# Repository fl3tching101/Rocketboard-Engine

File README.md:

# Rocketboard-Engine
Board which carries the full brains/powerhouse of a keyboard.

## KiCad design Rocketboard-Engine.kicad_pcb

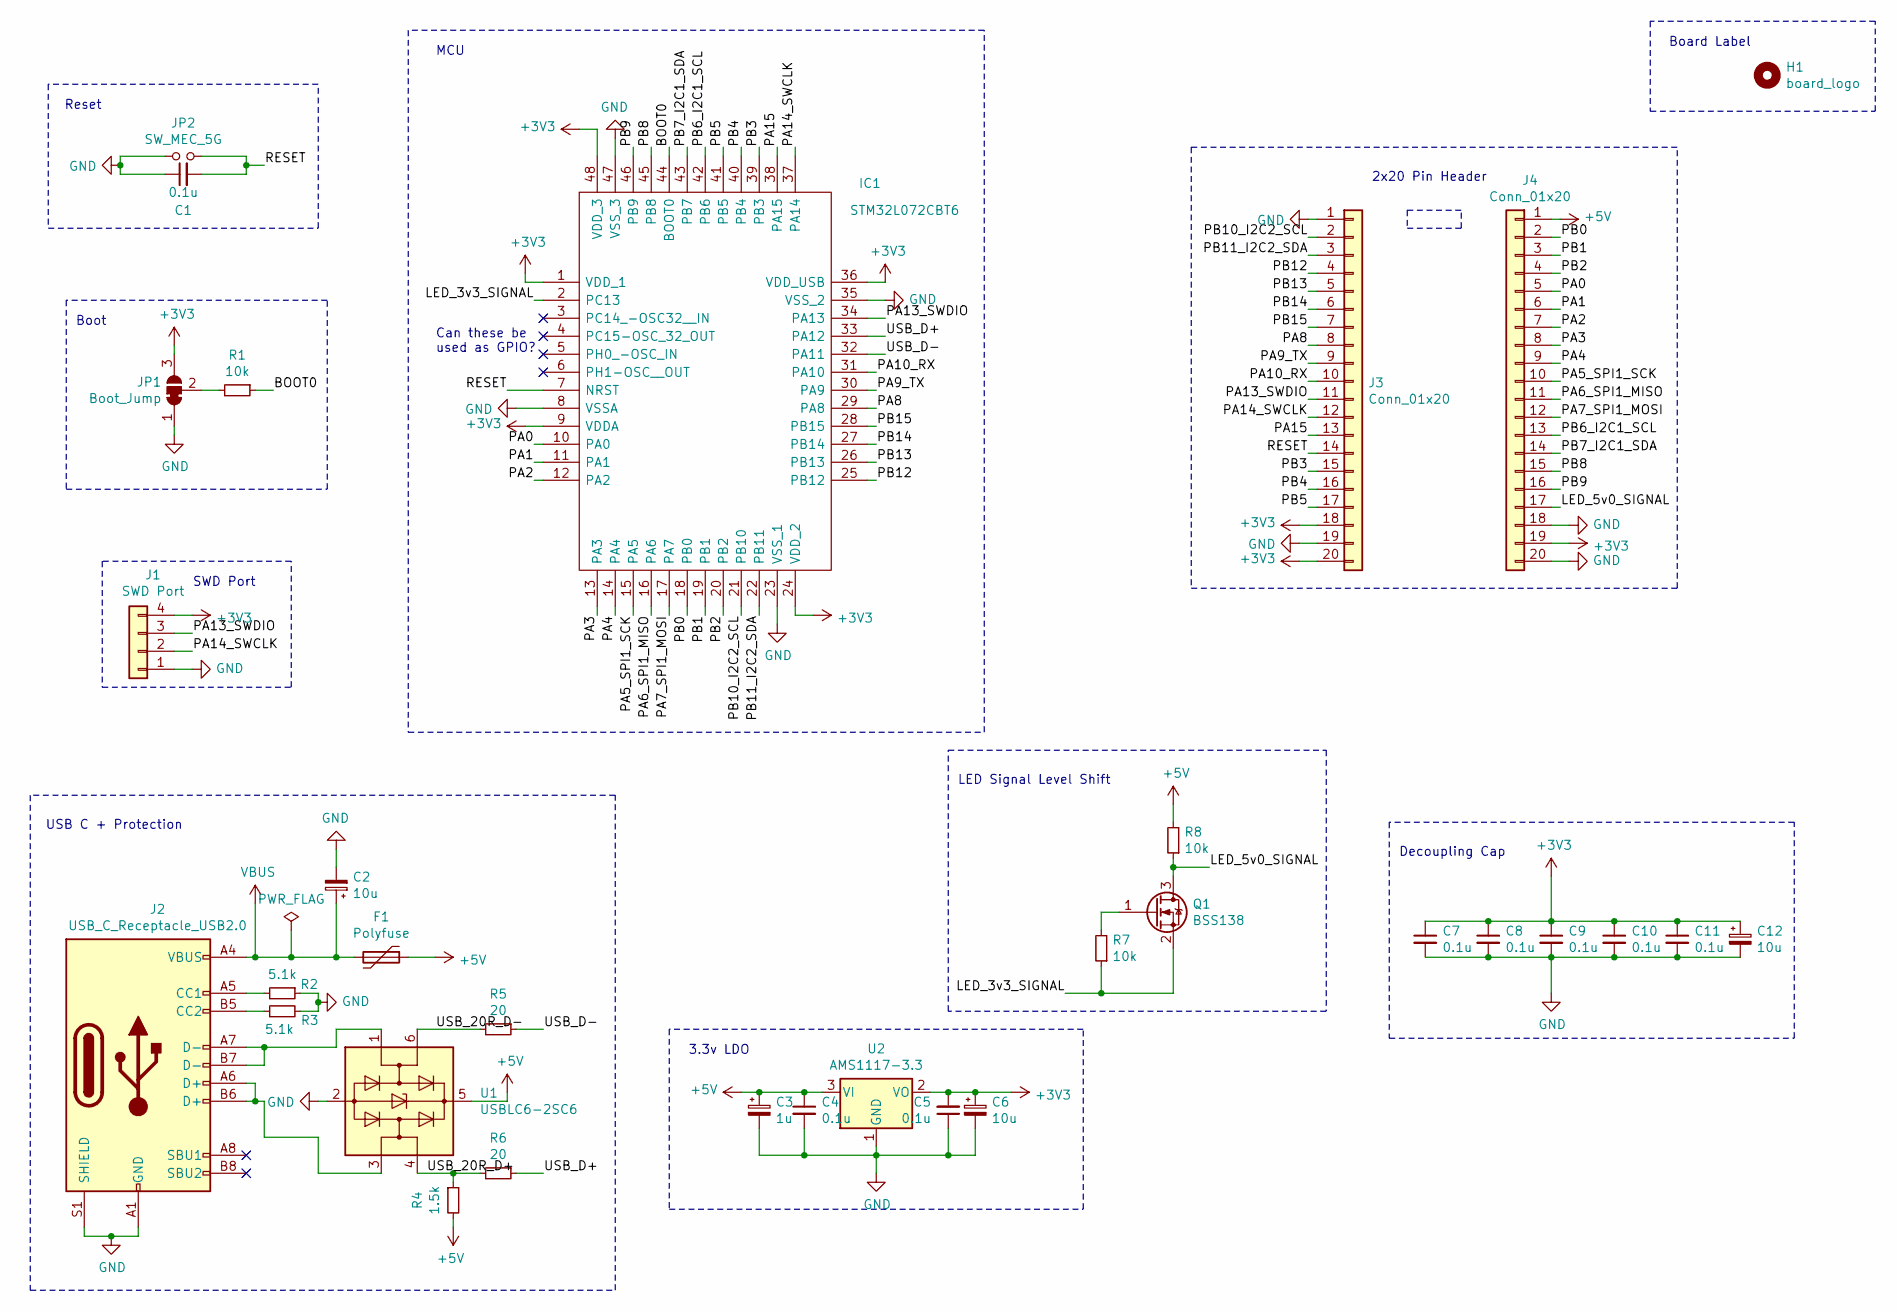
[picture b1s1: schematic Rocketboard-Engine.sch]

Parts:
C1, C4, C5, C7, C8, C9, C10, C11: 0.1u; C_0402_1005Metric
C2, C6, C12: 10u; CP_EIA-3216-10_Kemet-I
C3: 1u; C_0603_1608Metric
F1: Polyfuse; R_0805_2012Metric
H1: board_logo; board-title
IC1: STM32L072CBT6; LQFP-48_7x7mm_P0.5mm; Manufacturer_Part_Number STM32L072CBT6; Mouser Part Number 511-STM32L072CBT6
J1: SWD Port; PinHeader_1x04_P2.54mm_Vertical
J2: USB_C_Receptacle_USB2.0; USB_C_Receptacle_Palconn_UTC16-G
J3, J4: Conn_01x20; PinHeader_1x20_P2.54mm_Vertical
JP1: Boot_Jump; SolderJumper-3_P1.3mm_Bridged12_Pad1.0x1.5mm
JP2: SW_MEC_5G; SolderJumper-2_P1.3mm_Open_Pad1.0x1.5mm
Q1: BSS138; SOT-23
R1, R7, R8: 10k; R_0603_1608Metric
R2, R3: 5.1k; R_0603_1608Metric
R4: 1.5k; R_0603_1608Metric
R5, R6: 20; R_0603_1608Metric
U1: USBLC6-2SC6; SOT-23-6
U2: AMS1117-3.3; SOT-223-3_TabPin2

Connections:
+3V3: C5.2, C6.1, C7.1, C8.1, C9.1, C10.1, C11.1, C12.1, IC1.1 (VDD_1), IC1.9 (VDDA), IC1.24 (VDD_2), IC1.36 (VDD_USB), IC1.48 (VDD_3), J1.4, J3.18, J3.20, J4.19, JP1.3 (B), U2.2 (VO)
+5V: C3.1, C4.1, F1.1, J4.1, R4.2, R8.2, U1.5 (VBUS), U2.3 (VI)
/BOOT0: IC1.44 (BOOT0), R1.1
/LED_3v3_SIGNAL: IC1.2 (PC13), Q1.2 (S), R7.1
/LED_5v0_SIGNAL: J4.17, Q1.3 (D), R8.1
/PA0: IC1.10 (PA0), J4.5
/PA1: IC1.11 (PA1), J4.6
/PA2: IC1.12 (PA2), J4.7
/PA3: IC1.13 (PA3), J4.8
/PA4: IC1.14 (PA4), J4.9
/PA5_SPI1_SCK: IC1.15 (PA5), J4.10
/PA6_SPI1_MISO: IC1.16 (PA6), J4.11
/PA7_SPI1_MOSI: IC1.17 (PA7), J4.12
/PA8: IC1.29 (PA8), J3.8
/PA9_TX: IC1.30 (PA9), J3.9
/PA10_RX: IC1.31 (PA10), J3.10
/PA13_SWDIO: IC1.34 (PA13), J1.3, J3.11
/PA14_SWCLK: IC1.37 (PA14), J1.2, J3.12
/PA15: IC1.38 (PA15), J3.13
/PB0: IC1.18 (PB0), J4.2
/PB1: IC1.19 (PB1), J4.3
/PB2: IC1.20 (PB2), J4.4
/PB3: IC1.39 (PB3), J3.15
/PB4: IC1.40 (PB4), J3.16
/PB5: IC1.41 (PB5), J3.17
/PB6_I2C1_SCL: IC1.42 (PB6), J4.13
/PB7_I2C1_SDA: IC1.43 (PB7), J4.14
/PB8: IC1.45 (PB8), J4.15
/PB9: IC1.46 (PB9), J4.16
/PB10_I2C2_SCL: IC1.21 (PB10), J3.2
/PB11_I2C2_SDA: IC1.22 (PB11), J3.3
/PB12: IC1.25 (PB12), J3.4
/PB13: IC1.26 (PB13), J3.5
/PB14: IC1.27 (PB14), J3.6
/PB15: IC1.28 (PB15), J3.7
/RESET: C1.2, IC1.7 (NRST), J3.14, JP2.2
/USB_20R_D+: R4.1, R6.2, U1.4 (I/O2)
/USB_20R_D-: R5.2, U1.6 (I/O1)
/USB_D+: IC1.33 (PA12), R6.1
/USB_D-: IC1.32 (PA11), R5.1
GND: C1.1, C2.2, C3.2, C4.2, C5.1, C6.2, C7.2, C8.2, C9.2, C10.2, C11.2, C12.2, IC1.8 (VSSA), IC1.23 (VSS_1), IC1.35 (VSS_2), IC1.47 (VSS_3), J1.1, J2.A1 (GND), J2.A12 (GND), J2.B1 (GND), J2.B12 (GND), J2.S1 (SHIELD), J3.1, J3.19, J4.18, J4.20, JP1.1 (A), JP2.1, R2.1, R3.2, U1.2 (GND), U2.1 (GND)
unnamed: J2.A5 (CC1), R2.2
unnamed: J2.A6 (D+), J2.B6 (D+), U1.3 (I/O2)
unnamed: J2.A7 (D-), J2.B7 (D-), U1.1 (I/O1)
unnamed: J2.B5 (CC2), R3.1
unnamed: JP1.2 (C), R1.2
unnamed: Q1.1 (G), R7.2
VBUS: C2.1, F1.2, J2.A4 (VBUS), J2.A9 (VBUS), J2.B4 (VBUS), J2.B9 (VBUS)

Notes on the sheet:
3.3v LDO
USB C + Protection
Decoupling Cap
Reset
Boot
SWD Port
LED Signal Level Shift
Can these be used as GPIO?
MCU
2x20 Pin Header
Board Label

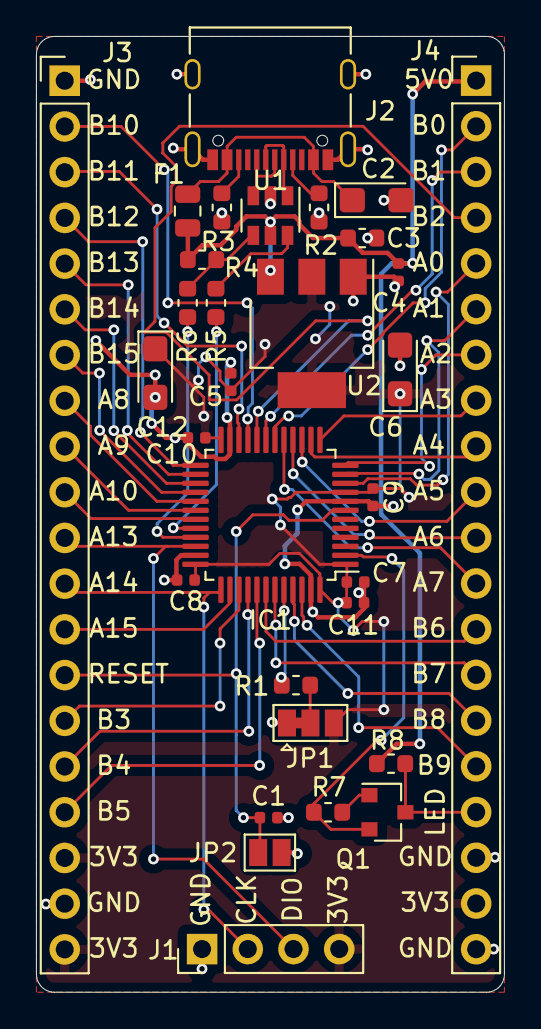
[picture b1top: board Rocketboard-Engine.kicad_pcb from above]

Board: 2 copper layers, 26.0 x 53.1 mm, 32 parts (1 on the bottom side), 48 nets.

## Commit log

2021-08-28 Preliminary design done
    Preliminary design work is done for schematic and layout, and updated gitignore to catch everything. Design may still need some tweaks, but is overall good.
2021-08-28 Fixed unconnected copper pours/nets
2021-08-28 Added silkscreen, fixed some placements, and generated gerbers
2021-08-28 Unknown change, but this is the state of ordered rev 1.0 boards
2021-09-07 Deleted unused comment
2021-12-11 Added images
2021-12-11 Add images to README
